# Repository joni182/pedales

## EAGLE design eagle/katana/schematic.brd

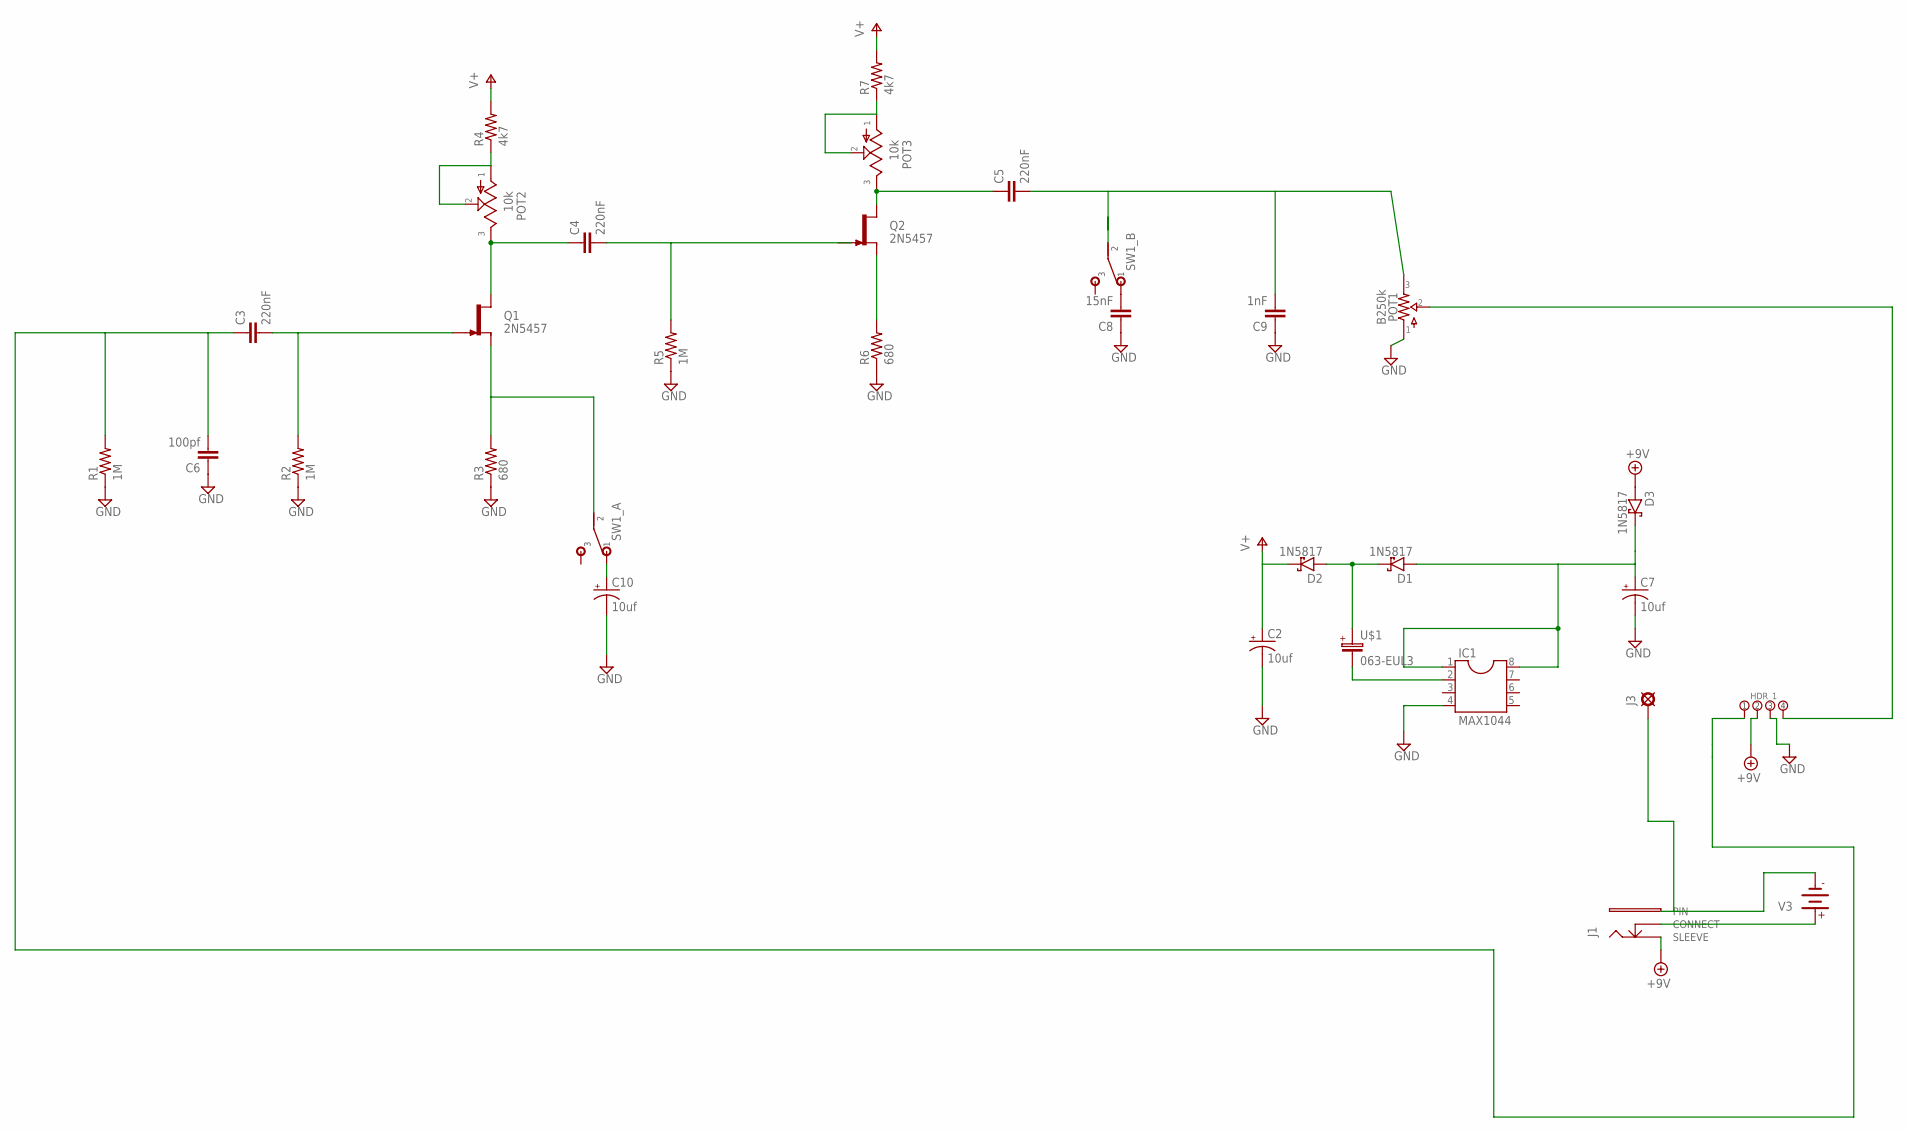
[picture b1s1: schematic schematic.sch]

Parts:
C2, C7, C10: 10uf; 050_020_1
C3, C4, C5: 220nF; 072X025
C6: 100pf; 072X025
C8: 15nF; 072X025
C9: 1nF; 072X025
D1, D2, D3: 1N5817; DO41-3
HDR_1: 4PIN
IC1: MAX1044; DIL08
J1: DC; DC_POWER_JACK
J3: PAD; SQUARE
POT1: B250k; 16MM_B.MOUNT
POT2, POT3: 10k; B25P
Q1, Q2: 2N5457; TO92-
R1, R2, R5: 1M; 0703
R3, R6: 680; 0703
R4, R7: 4k7; 0703
SW1: DPDT.1; DPDT_SOLDER_LUG
U$1: 063-EUL3; 063_025_L3
V3: DC; AB9V

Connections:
+9V: D3.A, HDR_1.P$2 (2), J1.SLEEVE
GND: C2.-, C6.1, C7.-, C8.1, C9.1, C10.-, HDR_1.P$3 (3), IC1.4, POT1.1, R1.1, R2.1, R3.1, R5.1, R6.1
unnamed: IC1.2, U$1.-
unnamed: D1.C, D2.A, U$1.+
unnamed: J1.CLOSE (CONNECT), V3.+
unnamed: C4.1, POT2.3, Q1.3 (D)
unnamed: Q1.2 (S), R3.2, SW1.A2 (2)
unnamed: C5.2, C9.2, POT1.3, SW1.B2 (2)
unnamed: Q2.2 (S), R6.2
unnamed: C4.2, R5.2
unnamed: C5.1, POT3.3, Q2.3 (D)
unnamed: C10.+, SW1.A1 (1)
unnamed: C8.2, SW1.B1 (1)
unnamed: POT2.1, POT2.2, R4.1
unnamed: POT3.1, POT3.2, R7.1
unnamed: J1.PIN, J3.1, V3.-
unnamed: C7.+, D1.A, D3.C, IC1.1, IC1.8
unnamed: C3.2, Q1.1 (G), R2.2
unnamed: C3.1, C6.2, HDR_1.P$1 (1), R1.2
unnamed: HDR_1.P$4 (4), POT1.2
V+: C2.+, D2.C, R4.2, R7.2

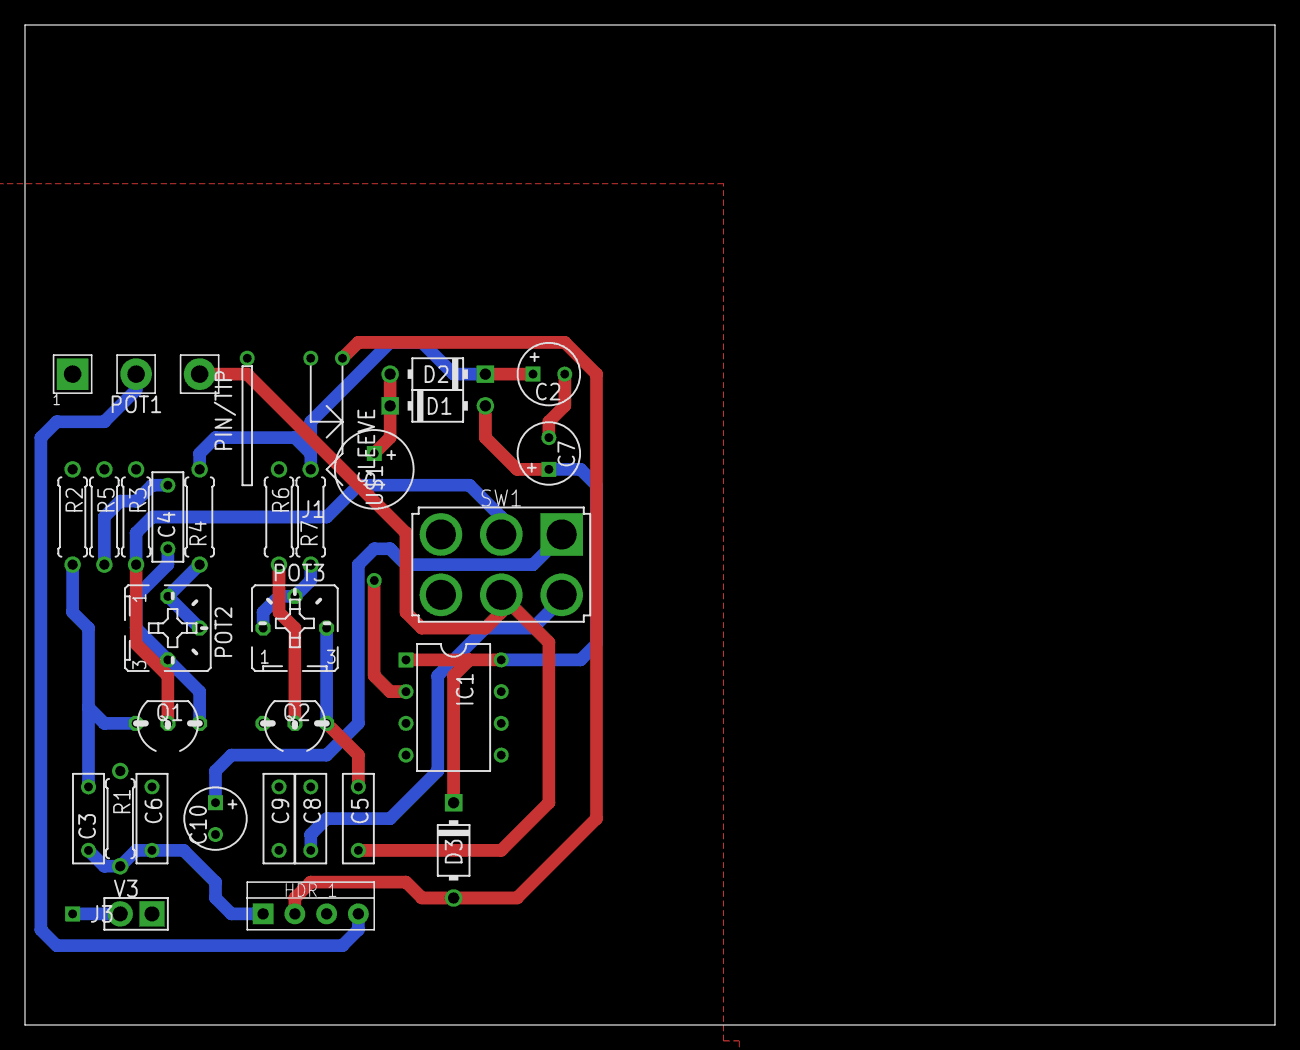
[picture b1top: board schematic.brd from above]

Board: 2 copper layers, 100.0 x 80.0 mm, 31 parts (0 on the bottom side), 21 nets.

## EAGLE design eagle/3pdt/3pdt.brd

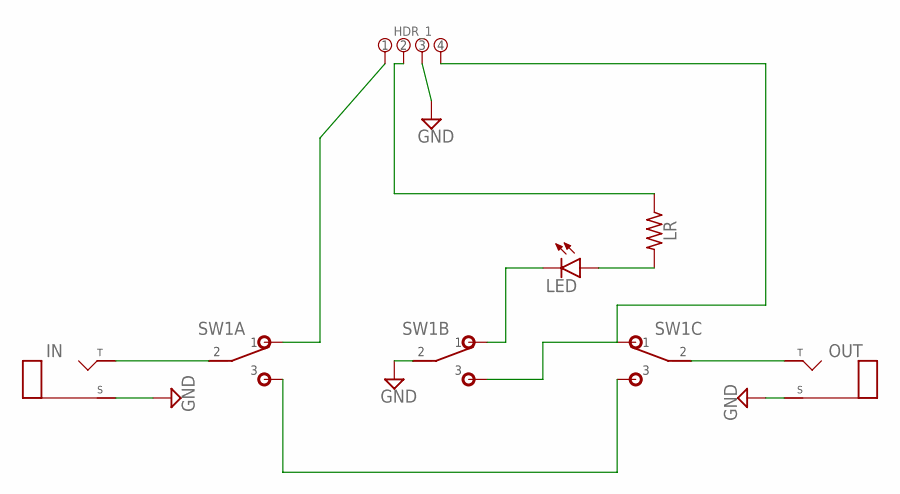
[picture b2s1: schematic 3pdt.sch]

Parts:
HDR_1: 4PIN
IN: MONO; TWO_PADS
LED: LED; 3MM_D
LR: R_.1; R0207/1V
OUT: MONO; TWO_PADS
SW1: 3PDT

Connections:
GND: HDR_1.P$3 (3), IN.S (SLEEVE), OUT.S (SLEEVE), SW1.B2 (2)
unnamed: LED.ANODE (A), LR.2
unnamed: SW1.A3 (3), SW1.C3 (3)
unnamed: OUT.T (TIP), SW1.C2 (2)
unnamed: IN.T (TIP), SW1.A2 (2)
unnamed: HDR_1.P$4 (4), SW1.B3 (3), SW1.C1 (1)
unnamed: LED.P$1 (C), SW1.B1 (1)
unnamed: HDR_1.P$2 (2), LR.1
unnamed: HDR_1.P$1 (1), SW1.A1 (1)

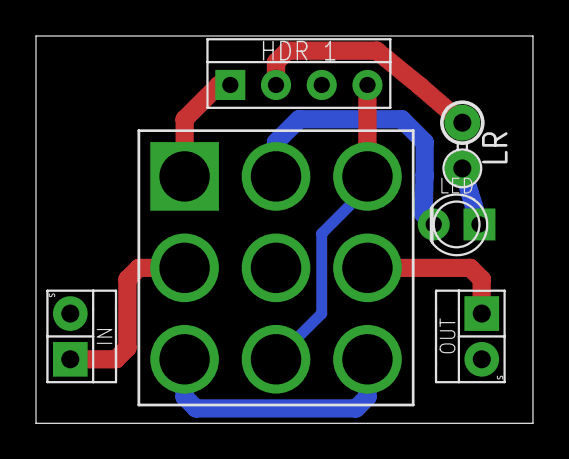
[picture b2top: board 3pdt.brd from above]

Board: 2 copper layers, 27.6 x 21.5 mm, 6 parts (0 on the bottom side), 9 nets.

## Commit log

2018-07-26 Carga inicial
2018-07-30 Esquematico del keeley katana
2018-07-31 Se ha modificado esquematico y creado layout
2019-02-26 Resistencias
2019-02-26 Faltan cosas
2019-02-27 Todo
2019-02-27 ahora se
